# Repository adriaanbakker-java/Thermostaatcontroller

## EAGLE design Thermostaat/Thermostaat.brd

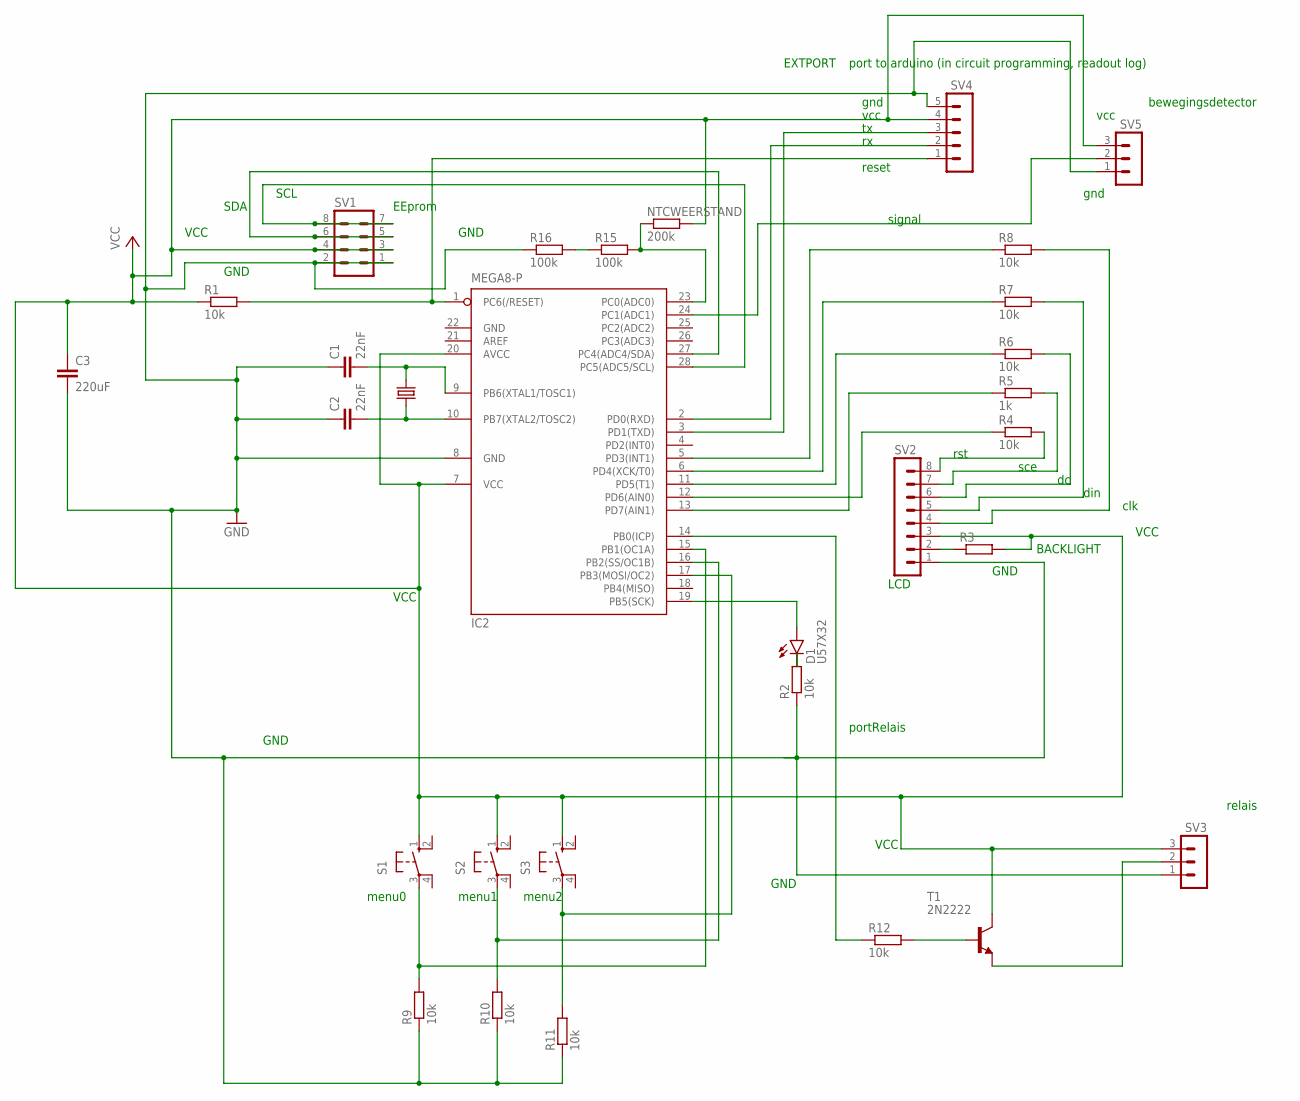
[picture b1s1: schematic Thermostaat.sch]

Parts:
C1, C2: 22nF; C2.5-2
C3: 220uF; C5B5.5
D1: U57X32
IC2: MEGA8-P; DIL28-3
NTCWEERSTAND: 200k; 0204/7
Q1: CRYSTALHC49U-V; HC49U-V
R1, R2, R4, R6, R7, R8, R9, R10, R11, R12: 10k; 0204/7
R3: R-EU_0204/7; 0204/7
R5: 1k; 0204/7
R15, R16: 100k; 0204/7
S1, S2, S3: 10-XX; B3F-10XX
SV1: MA04-2
SV2: MA08-1
SV3, SV5: MA03-1
SV4: MA05-1
T1: 2N2222; TO18

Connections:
GND: C1.1, C2.1, C3.2, IC2.8 (GND), IC2.22 (GND), R2.1, R9.1, R10.1, R11.1, R16.1, SV1.1, SV1.2, SV2.1, SV3.1, SV4.5, SV5.1
unnamed: IC2.1 (PC6(/RESET)), R1.2, SV4.1
unnamed: C2.2, IC2.10 (PB7(XTAL2/TOSC2)), Q1.2
unnamed: C1.2, IC2.9 (PB6(XTAL1/TOSC1)), Q1.1
unnamed: IC2.28 (PC5(ADC5/SCL)), SV1.7, SV1.8
unnamed: IC2.24 (PC1(ADC1)), SV5.2
unnamed: D1.A, IC2.19 (PB5(SCK))
unnamed: D1.K (C), R2.2
unnamed: R3.1, SV2.2
unnamed: R8.2, SV2.4
unnamed: R7.2, SV2.5
unnamed: R6.2, SV2.6
unnamed: R5.2, SV2.7
unnamed: R4.2, SV2.8
unnamed: IC2.5 (PD3(INT1)), R8.1
unnamed: IC2.6 (PD4(XCK/T0)), R7.1
unnamed: IC2.11 (PD5(T1)), R6.1
unnamed: IC2.13 (PD7(AIN1)), R5.1
unnamed: SV3.2, T1.1 (E)
unnamed: R12.2, T1.2 (B)
unnamed: IC2.14 (PB0(ICP)), R12.1
unnamed: IC2.12 (PD6(AIN0)), R4.1
unnamed: IC2.2 (PD0(RXD)), SV4.2
unnamed: IC2.3 (PD1(TXD)), SV4.3
unnamed: IC2.17 (PB3(MOSI/OC2)), R11.2, S3.3
unnamed: IC2.16 (PB2(SS/OC1B)), R10.2, S2.3
unnamed: IC2.15 (PB1(OC1A)), R9.2, S1.3
unnamed: R15.1, R16.2
unnamed: IC2.23 (PC0(ADC0)), NTCWEERSTAND.1, R15.2
SCL: IC2.27 (PC4(ADC4/SDA)), SV1.5, SV1.6
VCC: C3.1, IC2.7 (VCC), IC2.20 (AVCC), NTCWEERSTAND.2, R1.1, R3.2, S1.1 (S), S2.1 (S), S3.1 (S), SV1.3, SV1.4, SV2.3, SV3.3, SV4.4, SV5.3, T1.3 (C)

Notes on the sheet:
EEprom
GND
VCC
SDA
SCL
BACKLIGHT
LCD
clk
din
sce
relais
portRelais
rst
EXTPORT
port to arduino (in circuit programming, readout log)
reset
vcc
gnd
menu0
menu1
menu2
bewegingsdetector
signal

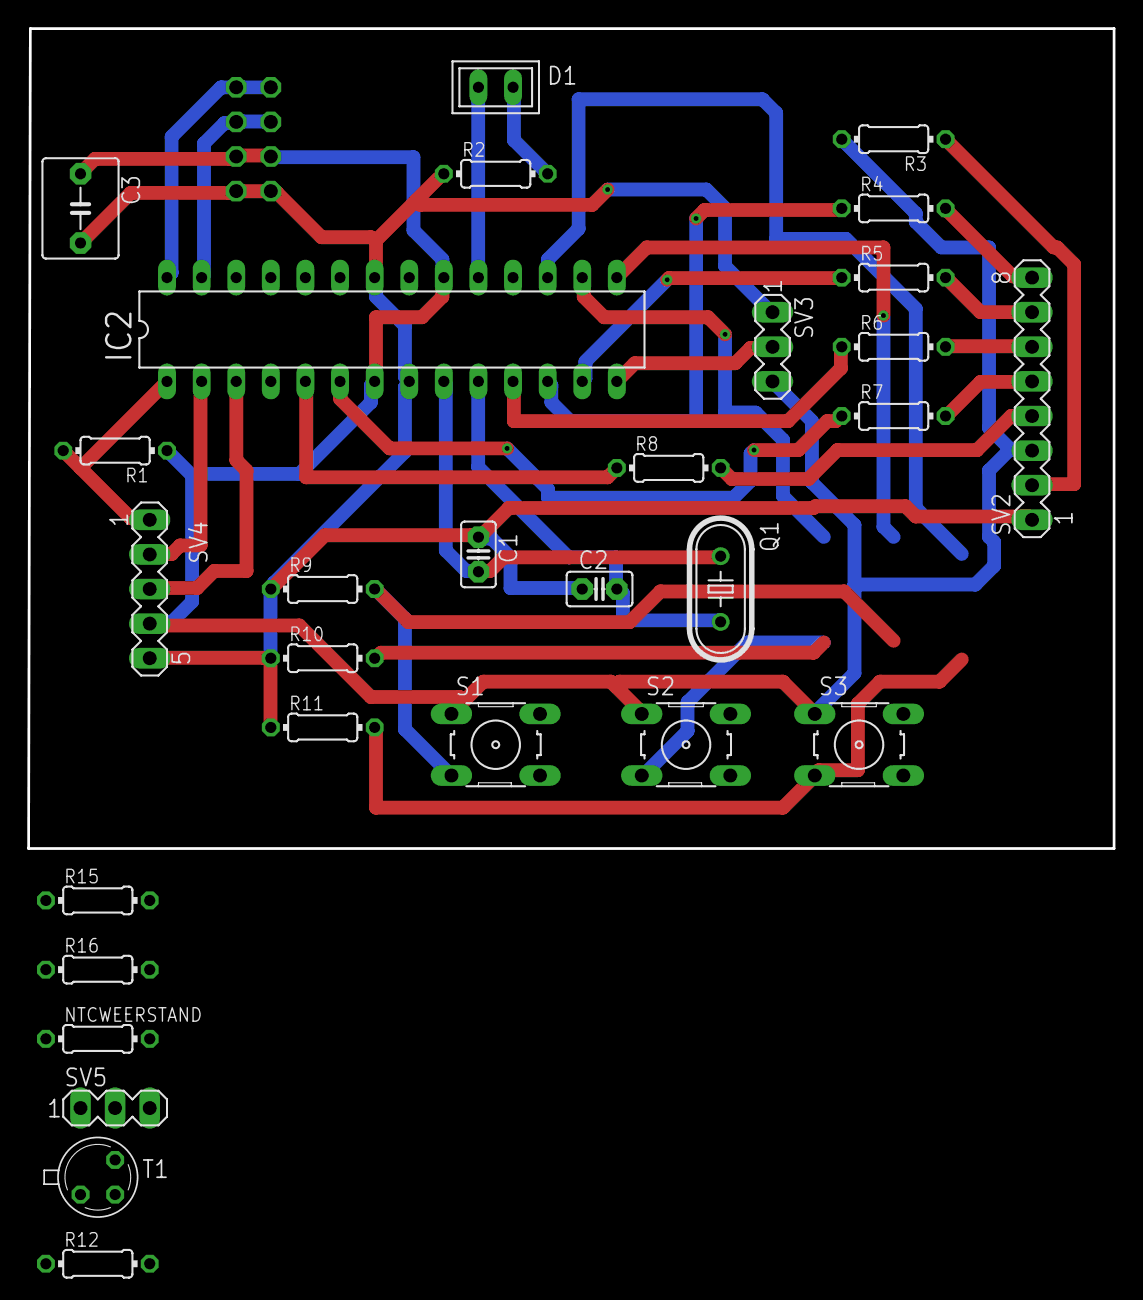
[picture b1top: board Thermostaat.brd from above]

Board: 2 copper layers, 79.7 x 60.2 mm, 30 parts (1 on the bottom side), 31 nets.

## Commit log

2023-01-31 test
2023-02-01 bewegingsdetector
2023-02-05 transistor toegevoegd voor relais
2023-02-05 kachel class opnieuw, gaf wat problemen
2023-02-05 lcd en clock
2023-02-05 start thermostaatschema's
2023-02-06 rudimentaire versie klaar harde instellingen geen menu
2023-02-06 uit schema altijd kachel uit
2023-02-06 menu gestart
2023-02-06 temperaturen bijstellen
2023-02-06 temperaturen verstellen
2023-02-06 foutje instellen pauzetemps verbeterd
2023-02-07 timeouts verzetten klaar
2023-02-07 eerste versie klaar, bewegingsdetectie
2023-02-08 poort A1 vervangen door A2
2023-02-08 laatste eindjes, in gebruik genomen
2023-03-02 watchdog toegevoegd
